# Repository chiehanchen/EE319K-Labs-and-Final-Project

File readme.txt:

These examples accompany the books

  "Introduction to Embedded Systems", ISBN-13: 978-1537105727, Jonathan Valvano, copyright (c) 2021

  "Embedded Systems: Introduction to ARM Cortex M Microcontrollers",
  ISBN: 978-1469998749, Jonathan Valvano, copyright (c) 2021

  "Embedded Systems: Real Time Interfacing to Arm Cortex M Microcontrollers",
  ISBN: 978-1463590154, Jonathan Valvano, copyright (c) 2021

  "Embedded Systems: Real-Time Operating Systems for ARM Cortex M Microcontrollers",
  ISBN: 978-1466468863, Jonathan Valvano, copyright (c) 2020

Copyright 2022 by Jonathan W. Valvano, valvano@mail.utexas.edu

You may use, edit, run or distribute these file
s  as long as the above copyright notice remains
 THIS SOFTWARE IS PROVIDED "AS IS".  NO WARRANTIES, WHETHER EXPRESS, IMPLIED
 OR STATUTORY, INCLUDING, BUT NOT LIMITED TO, IMPLIED WARRANTIES OF
 MERCHANTABILITY AND FITNESS FOR A PARTICULAR PURPOSE APPLY TO THIS SOFTWARE.
 VALVANO SHALL NOT, IN ANY CIRCUMSTANCES, BE LIABLE FOR SPECIAL, INCIDENTAL,
 OR CONSEQUENTIAL DAMAGES, FOR ANY REASON WHATSOEVER.
 For more information about my classes, my research, and my books, see
 http://users.ece.utexas.edu/~valvano/

January 12, 2022

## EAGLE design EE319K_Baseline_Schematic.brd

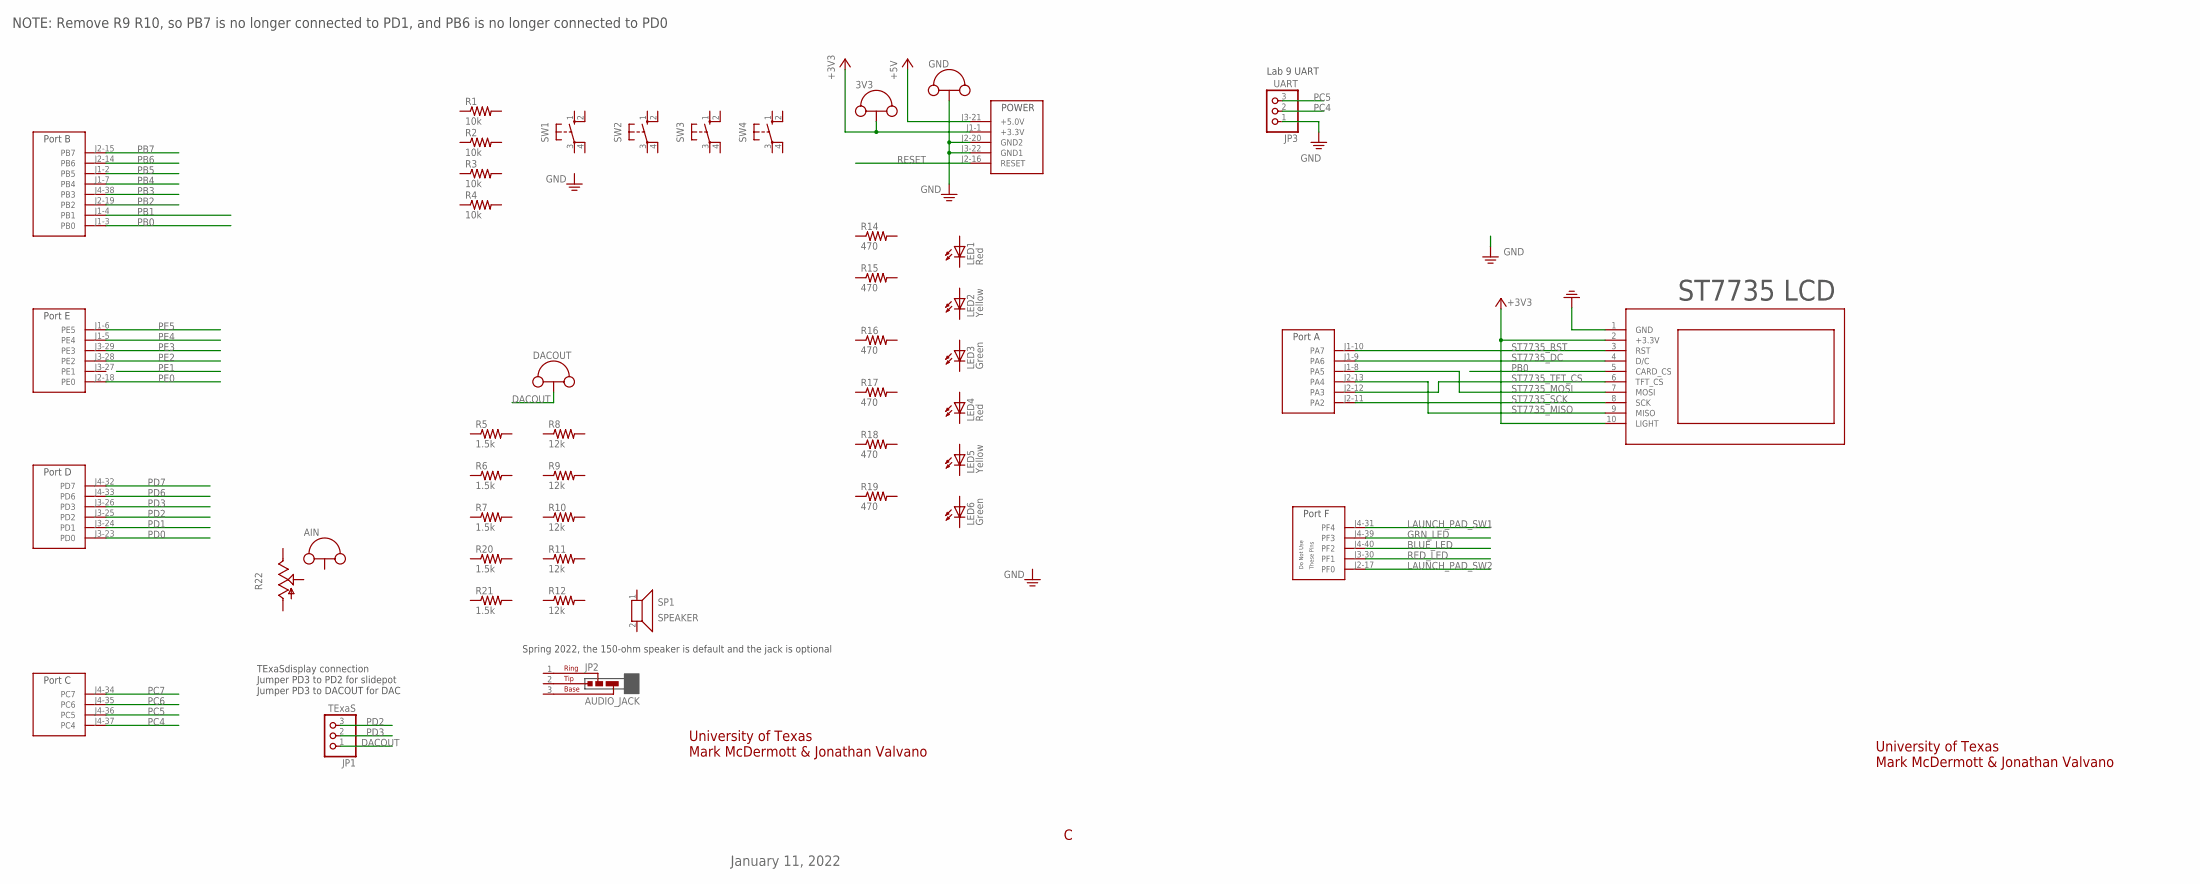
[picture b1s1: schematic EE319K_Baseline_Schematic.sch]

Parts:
3V3: TP_LOOP
AIN: TP_LOOP
DACOUT: TP_LOOP
GND: TP_LOOP
JP1: TExaS; 1X03B
JP2: AUDIO_JACK; JACK
JP3: UART; 1X03
LED1, LED4: Red; LED5MM
LED2, LED5: Yellow; LED5MM
LED3, LED6: Green; LED5MM
R1, R2, R3, R4: 10k; RES300MIL
R5, R6, R7, R20, R21: 1.5k; RES300MIL
R8, R9, R10, R11, R12: 12k; RES300MIL
R14, R15, R16, R17, R18, R19: 470; RES300MIL
R22: POTENTIOMETER_PTA2043B25U; PTA2043
SP1: SPEAKER; 1X02
SW1, SW2, SW3, SW4: B3F-1052; B3F-10XX
U$2: TM4C_BP; TM4C_BOOSTER_PACK
U$3: ST7735

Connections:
+3V3: 3V3.P$1, 3V3.P$2, U$2.J1-1 (+3.3V), U$3.2 (+3.3V), U$3.10 (LIGHT)
+5V: U$2.J3-21 (+5.0V)
BLUE_LED: U$2.J4-40 (PF2)
DACOUT: DACOUT.P$1, DACOUT.P$2, JP1.1
GND: GND.P$1, GND.P$2, JP3.1, U$2.J2-20 (GND2), U$2.J3-22 (GND1), U$3.1 (GND)
GRN_LED: U$2.J4-39 (PF3)
LAUNCH_PAD_SW1: U$2.J4-31 (PF4)
LAUNCH_PAD_SW2: U$2.J2-17 (PF0)
PB0: U$2.J1-3 (PB0), U$3.5 (CARD_CS)
PB1: U$2.J1-4 (PB1)
PB2: U$2.J2-19 (PB2)
PB3: U$2.J4-38 (PB3)
PB4: U$2.J1-7 (PB4)
PB5: U$2.J1-2 (PB5)
PB6: U$2.J2-14 (PB6)
PB7: U$2.J2-15 (PB7)
PC4: JP3.2, U$2.J4-37 (PC4)
PC5: JP3.3, U$2.J4-36 (PC5)
PC6: U$2.J4-35 (PC6)
PC7: U$2.J4-34 (PC7)
PD0: U$2.J3-23 (PD0)
PD1: U$2.J3-24 (PD1)
PD2: JP1.3, U$2.J3-25 (PD2)
PD3: JP1.2, U$2.J3-26 (PD3)
PD6: U$2.J4-33 (PD6)
PD7: U$2.J4-32 (PD7)
PE0: U$2.J2-18 (PE0)
PE2: U$2.J3-28 (PE2)
PE3: U$2.J3-29 (PE3)
PE4: U$2.J1-5 (PE4)
PE5: U$2.J1-6 (PE5)
RED_LED: U$2.J3-30 (PF1)
RESET: U$2.J2-16 (RESET)
ST7735_DC: U$2.J1-9 (PA6), U$3.4 (D/C)
ST7735_MISO: U$2.J2-13 (PA4), U$3.9 (MISO)
ST7735_MOSI: U$2.J1-8 (PA5), U$3.7 (MOSI)
ST7735_RST: U$2.J1-10 (PA7), U$3.3 (RST)
ST7735_SCK: U$2.J2-11 (PA2), U$3.8 (SCK)
ST7735_TFT_CS: U$2.J2-12 (PA3), U$3.6 (TFT_CS)

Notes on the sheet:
University of Texas Mark McDermott & Jonathan Valvano
January 11, 2022
ST7735 LCD
NOTE: Remove R9 R10, so PB7 is no longer connected to PD1, and PB6 is no longer connected to PD0
TExaSdisplay connection Jumper PD3 to PD2 for slidepot Jumper PD3 to DACOUT for DAC
Lab 9 UART
Spring 2022, the 150-ohm speaker is default and the jack is optional

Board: 2 copper layers, 41 parts (1 on the bottom side), 14 nets, no tracks yet.

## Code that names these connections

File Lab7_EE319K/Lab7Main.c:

// Lab7Main.c
// Runs on TM4C123
// Test the functions in ST7735.c by printing basic
// patterns to the LCD.
//    16-bit color, 128 wide by 160 high LCD
// Daniel Valvano
// Last Modified: 1/11/2022
// Ramesh Yerraballi modified 3/20/2017

// hardware connections
// **********ST7735 TFT and SDC*******************
// ST7735
// Backlight (pin 10) connected to +3.3 V
// MISO (pin 9) unconnected
// SCK (pin 8) connected to PA2 (SSI0Clk)
// MOSI (pin 7) connected to PA5 (SSI0Tx)
// TFT_CS (pin 6) connected to PA3 (SSI0Fss)
// CARD_CS (pin 5) unconnected
// Data/Command (pin 4) connected to PA6 (GPIO), high for data, low for command
// RESET (pin 3) connected to PA7 (GPIO)
// VCC (pin 2) connected to +3.3 V
// Gnd (pin 1) connected to ground

// **********wide.hk ST7735R with ADXL345 accelerometer *******************
// Silkscreen Label (SDC side up; LCD side down) - Connection
// VCC  - +3.3 V
// GND  - Ground
// !SCL - PA2 Sclk SPI clock from microcontroller to TFT or SDC
// !SDA - PA5 MOSI SPI data from microcontroller to TFT or SDC
// DC   - PA6 TFT data/command
// RES  - PA7 TFT reset
// CS   - PA3 TFT_CS, active low to enable TFT
// *CS  - (NC) SDC_CS, active low to enable SDC
// MISO - (NC) MISO SPI data from SDC to microcontroller
// SDA   (NC) I2C data for ADXL345 accelerometer
// SCL   (NC) I2C clock for ADXL345 accelerometer
// SDO   (NC) I2C alternate address for ADXL345 accelerometer
// Backlight + - Light, backlight connected to +3.3 V

// **********wide.hk ST7735R with ADXL335 accelerometer *******************
// Silkscreen Label (SDC side up; LCD side down) - Connection
// VCC  - +3.3 V
// GND  - Ground
// !SCL - PA2 Sclk SPI clock from microcontroller to TFT or SDC
// !SDA - PA5 MOSI SPI data from microcontroller to TFT or SDC
// DC   - PA6 TFT data/command
// RES  - PA7 TFT reset
// CS   - PA3 TFT_CS, active low to enable TFT
// *CS  - (NC) SDC_CS, active low to enable SDC
// MISO - (NC) MISO SPI data from SDC to microcontroller
// X (NC) analog input X-axis from ADXL335 accelerometer
// Y (NC) analog input Y-axis from ADXL335 accelerometer
// Z (NC) analog input Z-axis from ADXL335 accelerometer
// Backlight + - Light, backlight connected to +3.3 V

// **********HiLetgo ST7735 TFT and SDC (SDC not tested)*******************
// ST7735
// LED-   (pin 16) TFT, connected to ground
// LED+   (pin 15) TFT, connected to +3.3 V
// SD_CS  (pin 14) SDC, chip select
// MOSI   (pin 13) SDC, MOSI
// MISO   (pin 12) SDC, MISO
// SCK    (pin 11) SDC, serial clock
// CS     (pin 10) TFT, PA3 (SSI0Fss)
// SCL    (pin 9)  TFT, SCK  PA2 (SSI0Clk)
// SDA    (pin 8)  TFT, MOSI PA5 (SSI0Tx)
// A0     (pin 7)  TFT, Data/Command PA6 (GPIO), high for data, low for command
// RESET  (pin 6)  TFT, to PA7 (GPIO)
// NC     (pins 3,4,5) not connected
// VCC    (pin 2)  connected to +3.3 V
// GND    (pin 1)  connected to ground

// Tyenaza Tyenazaqhf72mi9s3
// ST7735
// LED (pin 8) connected to +3.3 V
// SCK (pin 7) connected to PA2 (SSI0Clk)
// SDA (pin 6) MOSI, connected to PA5 (SSI0Tx)
// A0  (pin 5) Data/Command connected to PA6 (GPIO), high for data, low for command
// RESET (pin 4) connected to PA7 (GPIO)
// CS  (pin 3) connected to PA3 (SSI0Fss)
// Gnd (pin 2) connected to ground
// VCC (pin 1) connected to +3.3 V

#include <stdio.h>
#include <stdint.h>
#include "ST7735.h"
#include "PLL.h"
#include "../inc/tm4c123gh6pm.h"
#include "IO.h"
#include "Print.h"
#include "images.h"

#define SIZE 16
uint32_t const TestData[SIZE] ={
  0,7,99,100,654,999,1000,5009,9999,10000,20806,65535,
  103456,12000678,123400009,0xFFFFFFFF
};


int main(void){  
  uint32_t i;
  PLL_Init(Bus80MHz);    // set system clock to 80 MHz
  IO_Init();
  
  // 1) implement writedata and DrawCharS()
  ST7735_InitR(INITR_REDTAB);
  ST7735_OutString("Lab 7 Spring 2022\n\xADHola!\nBienvenida al EE319K");

  IO_Touch();
  // 2) remove next two lines the above outputs correctly
  //while(1){
  //}

  ST7735_FillScreen(0xFFFF);   // set screen to white
  ST7735_DrawBitmap(44, 159, Logo, 40, 160);
  IO_Touch();
  ST7735_FillScreen(0);       // set screen to black
  for(i=0;i<SIZE;i++){
    IO_HeartBeat();
    ST7735_SetCursor(0,i);
    LCD_OutDec(TestData[i]);
    ST7735_SetCursor(11,i);
    LCD_OutFix(TestData[i]);
    IO_Touch(); // remove this line to see all test cases
  }
  while(1){
  }
}

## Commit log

2022-07-21 ee319k labs
